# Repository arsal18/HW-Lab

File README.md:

# HW-Lab
This reporsitory contains the lab work and the project of module Hardware Engineering. 

**Group Members:**  

- Arsal Abbasi  
- Ahmed Helmy  
- Jires Donfack Voufo

**PLEASE NOTE**

We have uploaded our complete alarm clock in the Project folder. There are three different folders in Project folder. 
-  **VHDL_Design** contains our alarm-clock design files on ModelSim, including testbench and simulation results.
-  **FPGA_Design** contatins our all source files from Vivado including the top file which is named Temp_on_7seg, the screenshots of synthesis results reports are also attached.
-  **PCB_Design** folder contains all files of our PCB design and schematic.

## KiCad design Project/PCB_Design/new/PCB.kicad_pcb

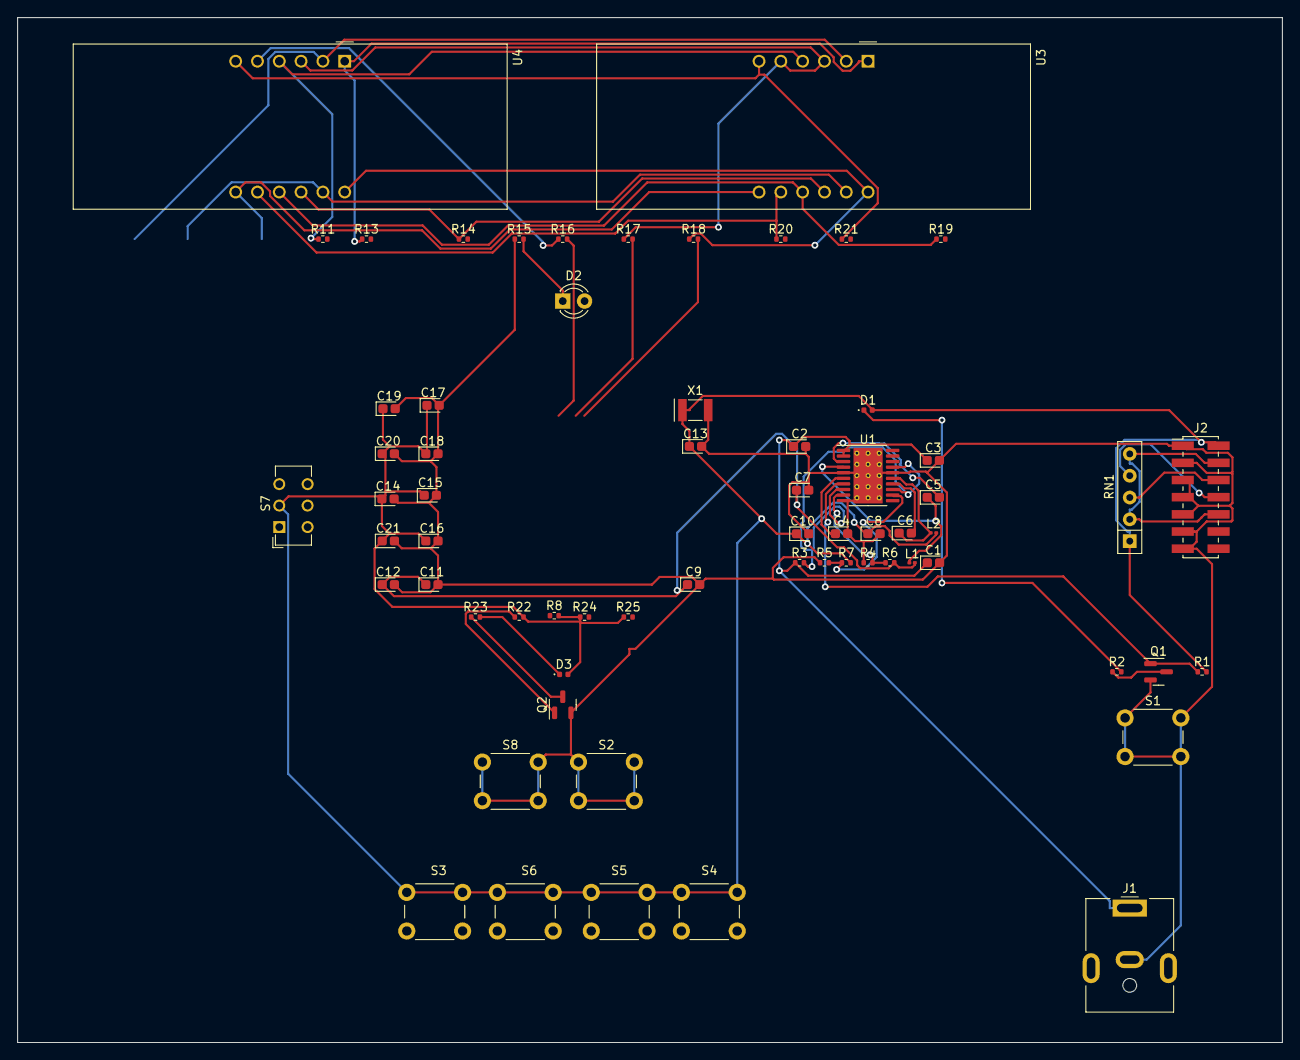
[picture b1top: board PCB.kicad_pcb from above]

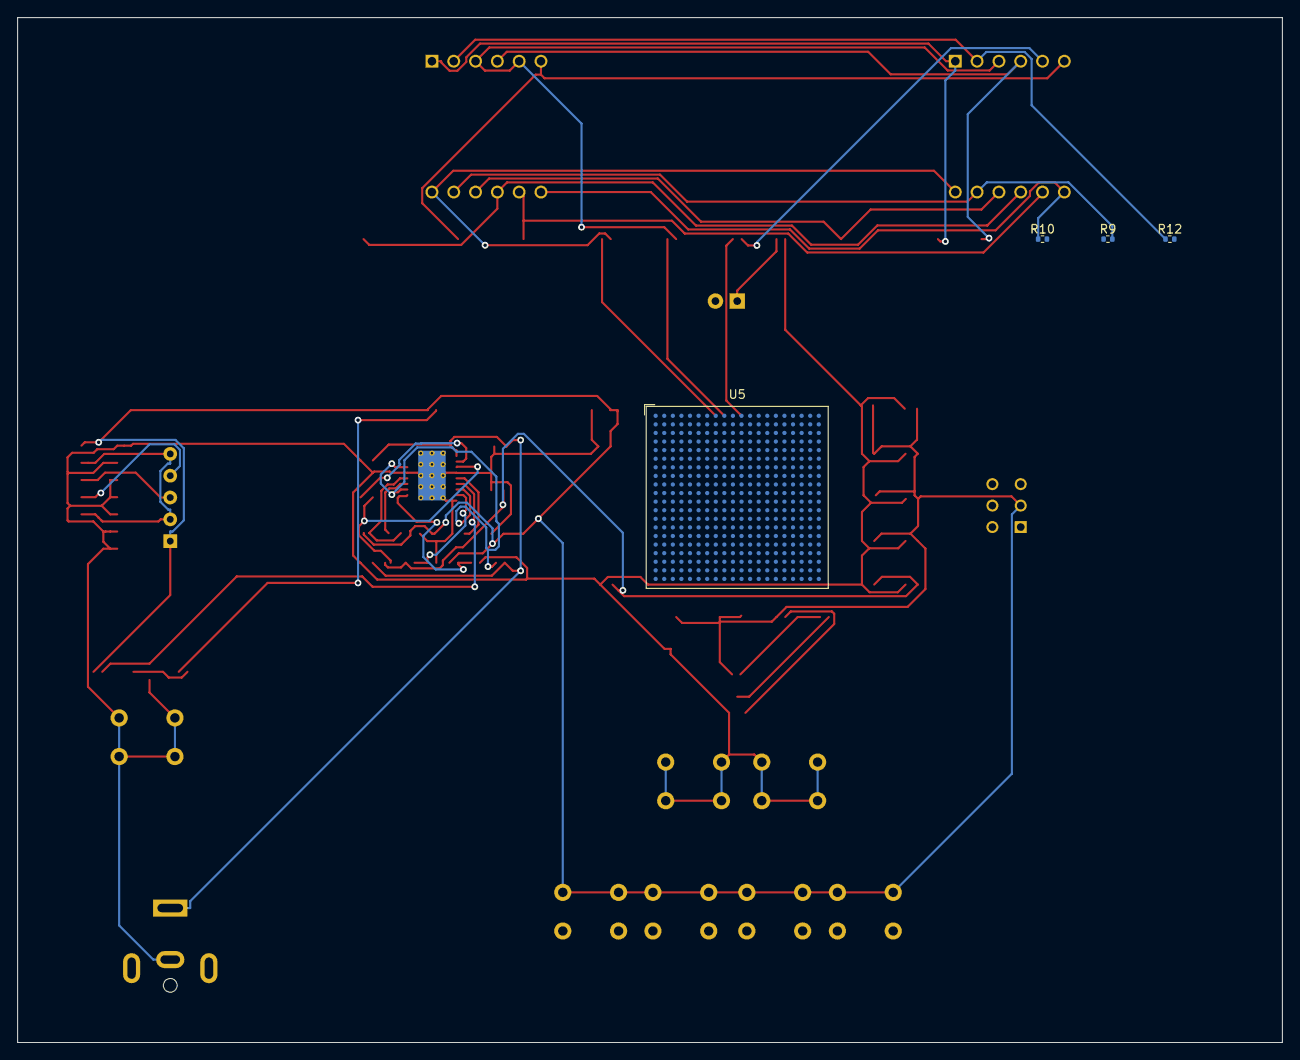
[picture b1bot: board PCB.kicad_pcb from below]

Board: 2 copper layers, 147.3 x 119.4 mm, 69 parts (4 on the bottom side), 46 nets.

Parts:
C1, C2, C3, C4, C5, C6, C7, C8, C9, C10, C11, C12, C13, C14, C15, C16, C17, C18, C19, C20, C21: C0603G104K5RACT250; CP_EIA-1608-08_AVX-J
D1, D3: LED_Small; LED_0402_1005Metric
D2: LED; LED_D3.0mm_Clear
J1: Barrel_Jack; BarrelJack_CUI_PJ-063AH_Horizontal
J2: XILINX_JTAG; PinHeader_2x07_P2.00mm_Vertical_SMD
L1, L2: INDUCTOR; L_0201_0603Metric
Q1, Q2: 2N7002E; SOT-23
R1, R2, R3, R4, R5, R6, R7, R8, R10, R11, R12, R13, R14, R15, R16, R17, R18, R19, R20, R21, R22, R23, R24, R25: ERJ3EKF3300V; R_0402_1005Metric
R9: 330; R_0402_1005Metric
RN1: R_Network04; R_Array_SIP5
S1, S2, S8: B3FS_1010P; SW_PUSH_6mm
S3, S4, S5, S6: 800AWSP9M2QE; SW_PUSH_6mm
S7: MINI-SPDT-SW; SW_CuK_JS202011CQN_DPDT_Straight
U1: TPS65581; HTSSOP-20-1EP_4.4x6.5mm_P0.65mm_EP3.4x6.5mm_Mask2.75x3.43mm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
U3, U4: CA56-12CGKWA
U5: XC7S50-FTGB196; BGA-400_21.0x21.0mm_Layout20x20_P1.0mm
X1: DSC61XX; Resonator_SMD_Murata_CDSCB-2Pin_4.5x2.0mm

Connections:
1.8V: C7.1, C9.1, C11.1, C12.1, L1.2, R6.2
3.3V: C8.1, C10.1, C13.1, C14.1, C15.1, C16.1, C17.1, C18.1, C19.1, C20.1, C21.1, D1.2 (A), D3.2 (A), J2.2 (VREF), L2.2, R1.2, R7.2, R8.2, R22.2, R24.1, R25.1, RN1.1 (common), S3.1, S4.1, S5.1, S6.1, S7.2, U5.G13 (VCCO_14), U5.K13 (VCCO_14), U5.N13 (VCCO_14), X1.1 (OE)
12V: C1.1, C2.1, C3.1, J1.1, R3.1, U1.1 (VIN), U1.2 (VIN)
/FPGA_utilities/JTAG_TCK: J2.8 (TDO), RN1.4 (R3)
/FPGA_utilities/JTAG_TDAO: J2.6 (TCK), RN1.3 (R2)
/FPGA_utilities/JTAG_TMS: J2.4 (TMS), J2.10 (TDI), RN1.2 (R1), RN1.5 (R4)
/FPGA_utilities/PGA_DONE: Q2.1 (G), R22.1
/Power/P_GOOD: Q1.1 (G), R1.1, U1.7 (PG)
GND: C1.2, C2.2, C3.2, C4.2, C7.2, C8.2, C9.2, C10.2, C11.2, C12.2, C13.2, C14.2, C15.2, C16.2, C17.2, C18.2, C19.2, C20.2, C21.2, J1.2, J2.1 (GND), J2.3 (GND), J2.5 (GND), J2.7 (GND), J2.9 (GND), J2.11 (GND), J2.13 (GND), Q1.2 (S), Q2.2 (S), R4.1, R5.1, R15.1, S1.1, S1.2, S2.1, S2.2, S8.1, S8.2, U1.5 (PGND1), U1.10 (GND), U1.16 (PGND3), U1.21 (PAD), X1.2 (GND)
unnamed: C4.1, U1.6 (VREG5)
unnamed: C6.1, L2.1, U1.15 (SW3)
unnamed: C6.2, U1.14 (VBST3)
unnamed: D2.1 (K), R15.2
unnamed: D2.2 (A), U5.M12 (IO_L20N_T3_D23_14)
unnamed: Q1.3 (D), R2.1
unnamed: Q2.3 (D), R23.1
unnamed: D1.1 (K), R2.2
unnamed: R5.2, R7.1, U1.12 (VFB3)
unnamed: R9.1, U5.E11 (IO_0_14)
unnamed: R9.2, U3.11 (a), U4.11 (a)
unnamed: R10.1, U3.7 (b), U4.7 (b)
unnamed: R10.2, U5.B11 (IO_L1P_T0_D00_MOSI_14)
unnamed: R11.1, U3.4 (c), U4.4 (c)
unnamed: R11.2, U5.B12 (IO_L1N_T0_D01_DIN_14)
unnamed: R12.1, U3.2 (d), U4.2 (d)
unnamed: R12.2, U5.D10 (IO_L2P_T0_D02_14)
unnamed: R13.1, U3.1 (e), U4.1 (e)
unnamed: R13.2, U5.C10 (IO_L2N_T0_D03_14)
unnamed: R14.1, U3.10 (f), U4.10 (f)
unnamed: R14.2, U5.B10 (IO_L3P_T0_DQS_PUDC_B_14)
unnamed: R16.1, U4.5 (g)
unnamed: R16.2, U5.A10 (IO_L3N_T0_DQS_EMCCLK_14)
unnamed: R17.1, U3.3 (DPX), U3.5 (g), U4.3 (DPX)
unnamed: R17.2, U5.A12 (IO_L4P_T0_D04_14)
unnamed: R18.1, U3.12 (CA1), U4.12 (CA1)
unnamed: R18.2, U5.A13 (IO_L4N_T0_D05_14)
unnamed: R19.1, U3.9 (CA2), U4.9 (CA2)
unnamed: R19.2, U5.B13 (IO_L5P_T0_D06_14)
unnamed: R20.1, U3.8 (CA3), U4.8 (CA3)
unnamed: R20.2, U5.B14 (IO_L5N_T0_D07_14)
unnamed: R21.1, U3.6 (CA4), U4.6 (CA4)
unnamed: R21.2, U5.F12 (IO_L7P_T1_D09_14)
unnamed: D3.1 (K), R23.2
unnamed: S7.1, U5.L13 (IO_L16N_T2_D31_14)
unnamed: S7.3, U5.J11 (IO_L17P_T2_D30_14)
SYSRES: R8.1, U5.H11 (IO_L13P_T2_MRCC_14)

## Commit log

2023-05-23 Create Exercise1
2023-05-23 Create 1bit_ha
2023-05-23 Create fulladder
2023-05-26 Create Project idea
2023-06-04 Create Lab3
2023-06-04 Create Exercise2
2023-06-04 Create ex
2023-06-04 Create exx
2023-06-04 Create exxxx
2023-06-04 Create ff
2023-06-04 Create ffff
2023-06-04 Create hhhh
2023-06-04 Create Decoder
2023-06-04 Create ripple carry adder
2023-06-04 Create Adder-Subtractor
2023-06-12 Create BCD
2023-06-12 Create 4 Bit BCD
2023-06-16 Create report
2023-06-17 Documentation Draft
2023-06-17 Create draft1
2023-06-17 Create file
2023-06-21 AlarmClock Slides
2023-06-21 Create ppt
2023-06-22 TB simulation on ModelSim
2023-06-22 Create vhdl
2023-06-29 Create newfile
2023-07-02 Create 4
2023-07-02 Create 1
2023-07-02 Create 2
2023-07-02 Create 3
2023-07-02 Create Running light
2023-07-02 Create counter
2023-07-04 Final Documentation
